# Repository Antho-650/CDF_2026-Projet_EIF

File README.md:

# CDF 2026 - Projet EIF

Dépôt officiel pour la participation à la Coupe de France de Robotique 2026.

## Documents et Suivi

Le suivi des achats (Excel/Google Sheets) et les documents administratifs sont sur le Google Drive du projet : https://drive.google.com/drive/u/1/folders/1xHnVBchuZF8TSyvHd5yfe0Ny8L7n_gqj

## Structure du dépôt

- **documents/** : Documents généraux du projet (spécifications, règlement, etc.)
- **robot_principal/** : Fichiers du robot principal
  - **electronique/** : Cartes électroniques (haut niveau, base mobile, actionneurs)
  - **mecanique/** : Conception mécanique (assemblage complet et sous-ensembles)
  - **code/** : Code embarqué (STM32) et code haut niveau (Raspberry Pi)
- **balises/** : Système de balises (électronique, code, mécanique)
- **pami_ninja/** : PAMI Ninja (électronique, mécanique, code)
- **pami_statique/** : PAMI Statique pour fin de match (électronique, mécanique, code)

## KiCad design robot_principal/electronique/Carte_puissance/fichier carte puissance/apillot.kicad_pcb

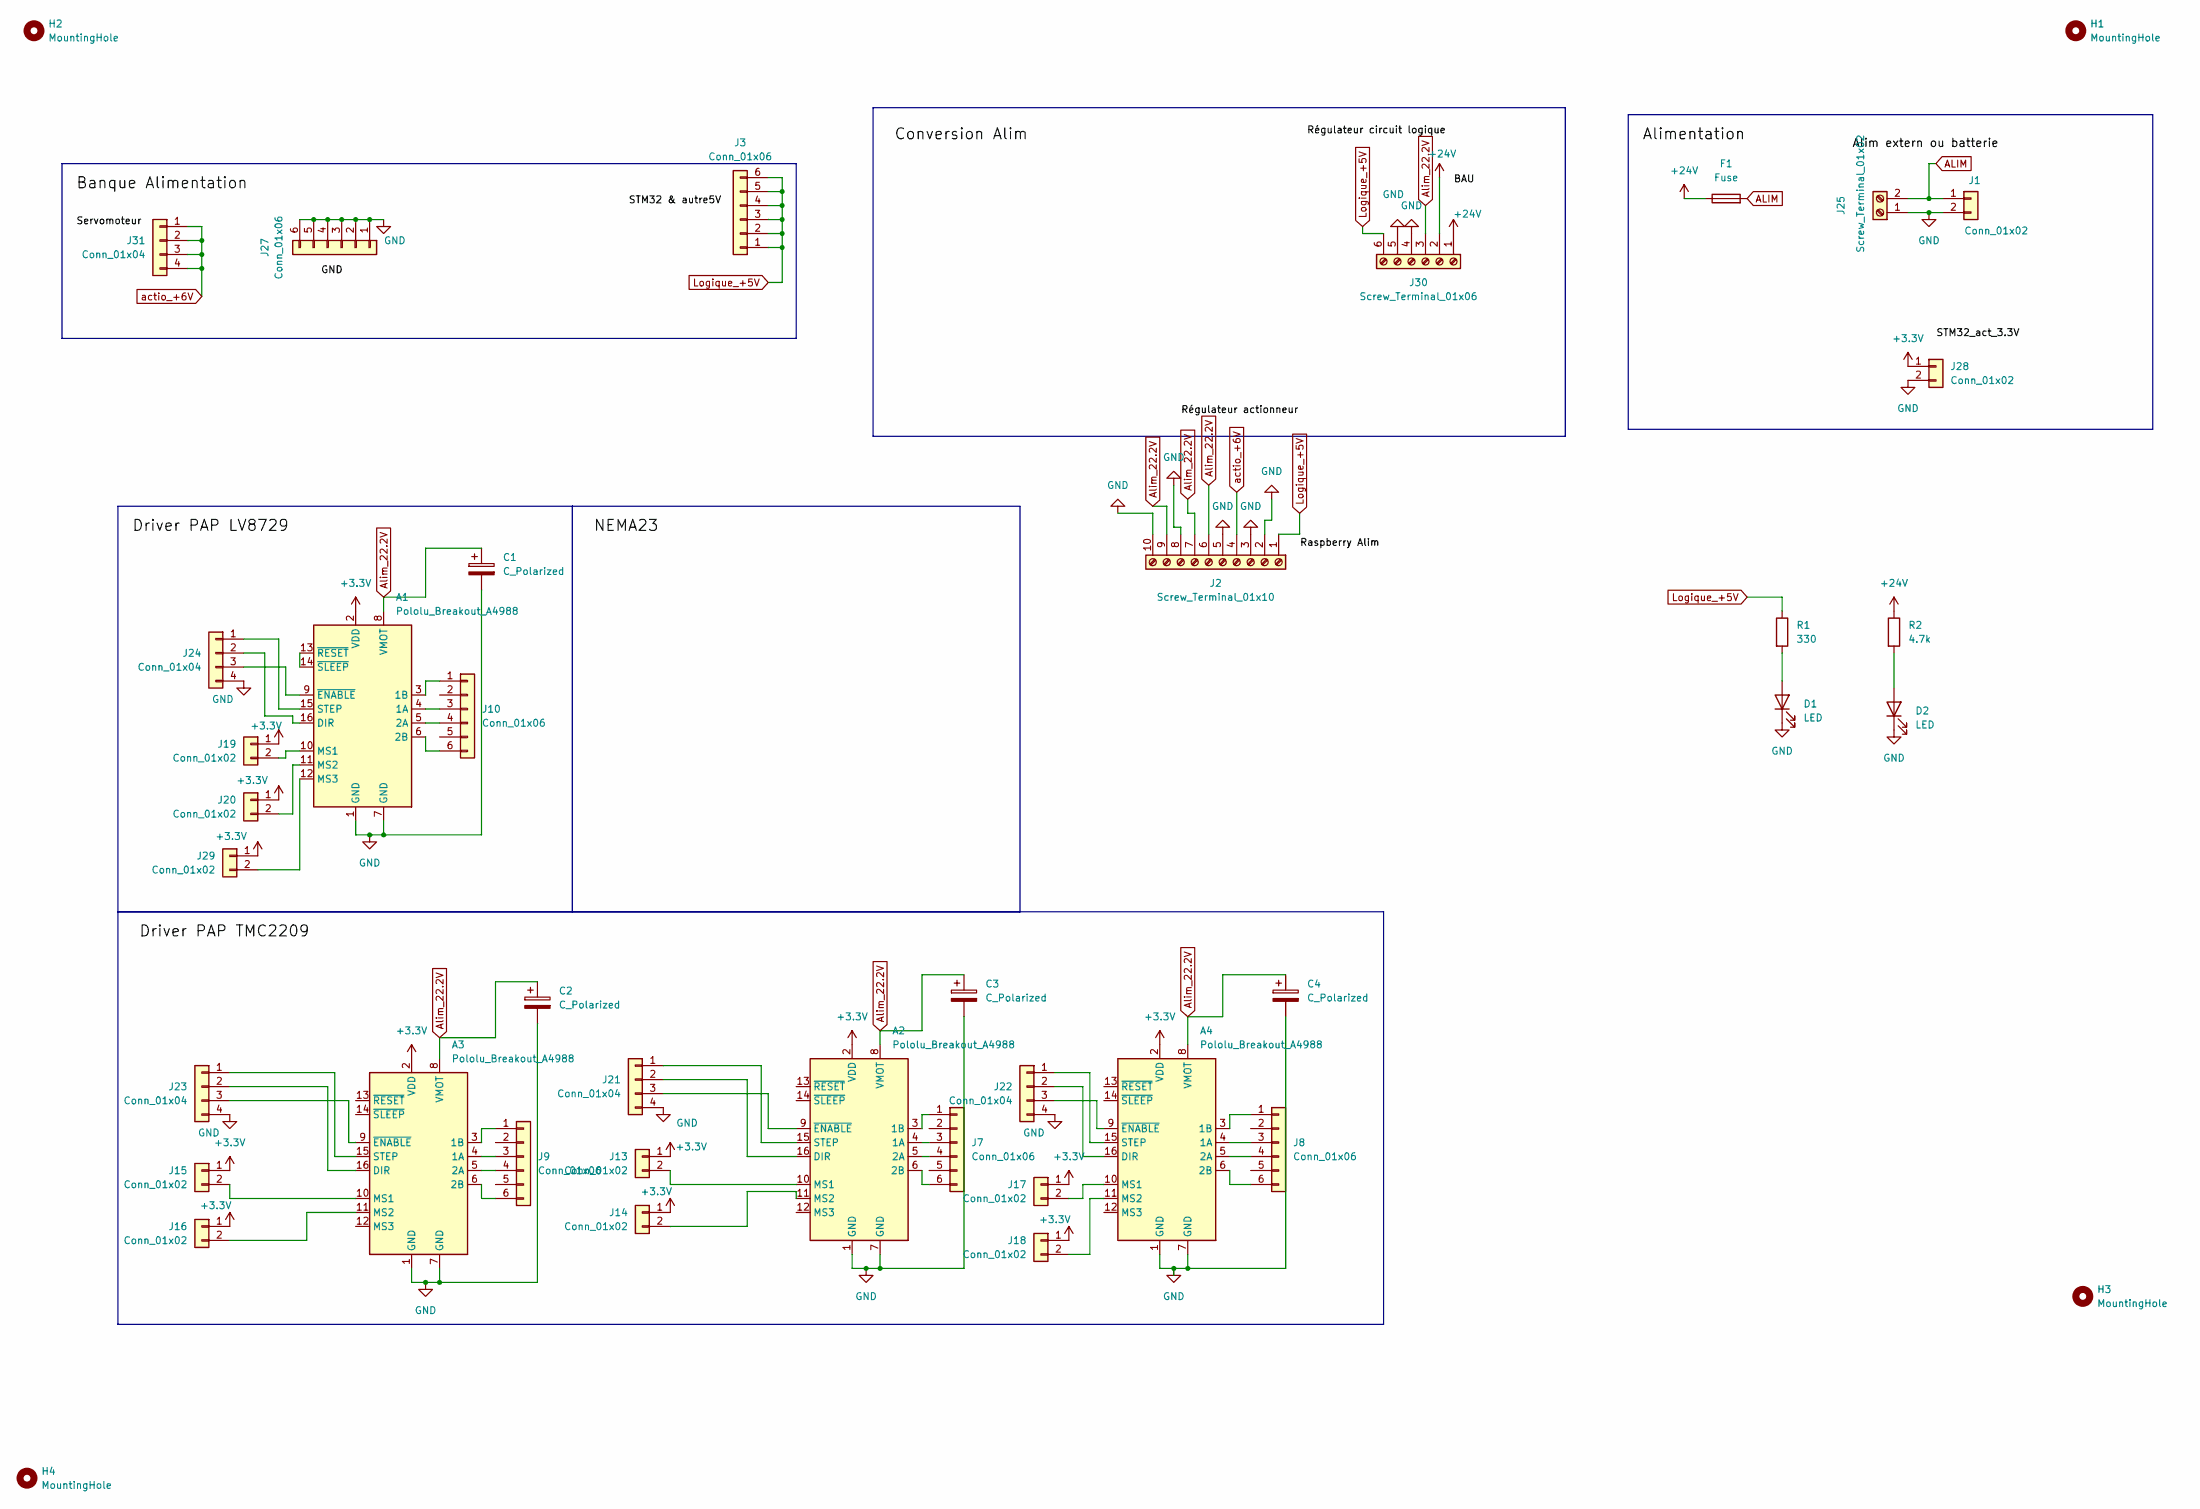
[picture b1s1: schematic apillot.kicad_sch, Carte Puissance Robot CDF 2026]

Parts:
A1, A2, A3, A4: Pololu_Breakout_A4988; Pololu_Breakout-16_15.2x20.3mm
C1, C2, C3, C4: C_Polarized; CP_Radial_D10.0mm_P5.00mm
D1, D2: LED; LED_D5.0mm
F1: Fuse; FuseHolder_Blade_ATO_Littelfuse_FLR_178.6165
H1, H2, H3, H4: MountingHole; MountingHole_3.2mm_M3
J1: Conn_01x02; AMASS_XT60-M_1x02_P7.20mm_Vertical
J2: Screw_Terminal_01x10; TerminalBlock_Phoenix_MKDS-1,5-10-5.08_1x10_P5.08mm_Horizon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
J3, J27: Conn_01x06; PinHeader_1x06_P2.54mm_Vertical
J7, J8, J9, J10: Conn_01x06; JST_XH_B6B-XH-A_1x06_P2.50mm_Vertical
J13, J14, J15, J16, J17, J18, J19, J20, J28, J29: Conn_01x02; PinHeader_1x02_P2.54mm_Vertical
J21, J22, J23, J24, J31: Conn_01x04; PinHeader_1x04_P2.54mm_Vertical
J25: Screw_Terminal_01x02; TerminalBlock_Phoenix_MKDS-1,5-2-5.08_1x02_P5.08mm_Horizont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
J30: Screw_Terminal_01x06; TerminalBlock_Phoenix_MKDS-1,5-6-5.08_1x06_P5.08mm_Horizont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
R1: 330; R_Axial_DIN0207_L6.3mm_D2.5mm_P10.16mm_Horizontal
R2: 4.7k; R_Axial_DIN0207_L6.3mm_D2.5mm_P10.16mm_Horizontal

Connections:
+3.3V: A1.2 (VDD), A2.2 (VDD), A3.2 (VDD), A4.2 (VDD), J13.1, J14.1, J15.1, J16.1, J17.1, J18.1, J19.1, J20.1, J28.1, J29.1
+24V: F1.1, J30.1, J30.2, R2.1
ALIM: F1.2, J1.1, J25.2
Alim_22.2V: A1.8 (VMOT), A2.8 (VMOT), A3.8 (VMOT), A4.8 (VMOT), C1.1, C2.1, C3.1, C4.1, J2.6, J2.7, J2.9, J30.3
GND: A1.1 (GND), A1.7 (GND), A2.1 (GND), A2.7 (GND), A3.1 (GND), A3.7 (GND), A4.1 (GND), A4.7 (GND), C1.2, C2.2, C3.2, C4.2, D1.1 (K), D2.1 (K), J1.2, J2.2, J2.3, J2.5, J2.8, J2.10, J21.4, J22.4, J23.4, J24.4, J25.1, J27.1, J27.2, J27.3, J27.4, J27.5, J27.6, J28.2, J30.4, J30.5
Logique_+5V: J2.1, J3.1, J3.2, J3.3, J3.4, J3.5, J3.6, J30.6, R1.1
unnamed: A1.4 (1A), J10.3
unnamed: A1.3 (1B), J10.1
unnamed: A1.5 (2A), J10.4
unnamed: A1.6 (2B), J10.6
unnamed: A1.16 (DIR), J24.2
unnamed: A1.10 (MS1), J19.2
unnamed: A1.11 (MS2), J20.2
unnamed: A1.12 (MS3), J29.2
unnamed: A1.15 (STEP), J24.1
unnamed: A1.9 (~ENABLE), J24.3
unnamed: A1.13 (~RESET), A1.14 (~SLEEP)
unnamed: A2.4 (1A), J7.3
unnamed: A2.3 (1B), J7.1
unnamed: A2.5 (2A), J7.4
unnamed: A2.6 (2B), J7.6
unnamed: A2.16 (DIR), J21.2
unnamed: A2.10 (MS1), J13.2
unnamed: A2.11 (MS2), J14.2
unnamed: A2.15 (STEP), J21.1
unnamed: A2.9 (~ENABLE), J21.3
unnamed: A3.4 (1A), J9.3
unnamed: A3.3 (1B), J9.1
unnamed: A3.5 (2A), J9.4
unnamed: A3.6 (2B), J9.6
unnamed: A3.16 (DIR), J23.2
unnamed: A3.10 (MS1), J15.2
unnamed: A3.11 (MS2), J16.2
unnamed: A3.15 (STEP), J23.1
unnamed: A3.9 (~ENABLE), J23.3
unnamed: A4.4 (1A), J8.3
unnamed: A4.3 (1B), J8.1
unnamed: A4.5 (2A), J8.4
unnamed: A4.6 (2B), J8.6
unnamed: A4.16 (DIR), J22.2
unnamed: A4.10 (MS1), J17.2
unnamed: A4.11 (MS2), J18.2
unnamed: A4.15 (STEP), J22.1
unnamed: A4.9 (~ENABLE), J22.3
unnamed: D1.2 (A), R1.2
unnamed: D2.2 (A), R2.2
actio_+6V: J2.4, J31.1, J31.2, J31.3, J31.4

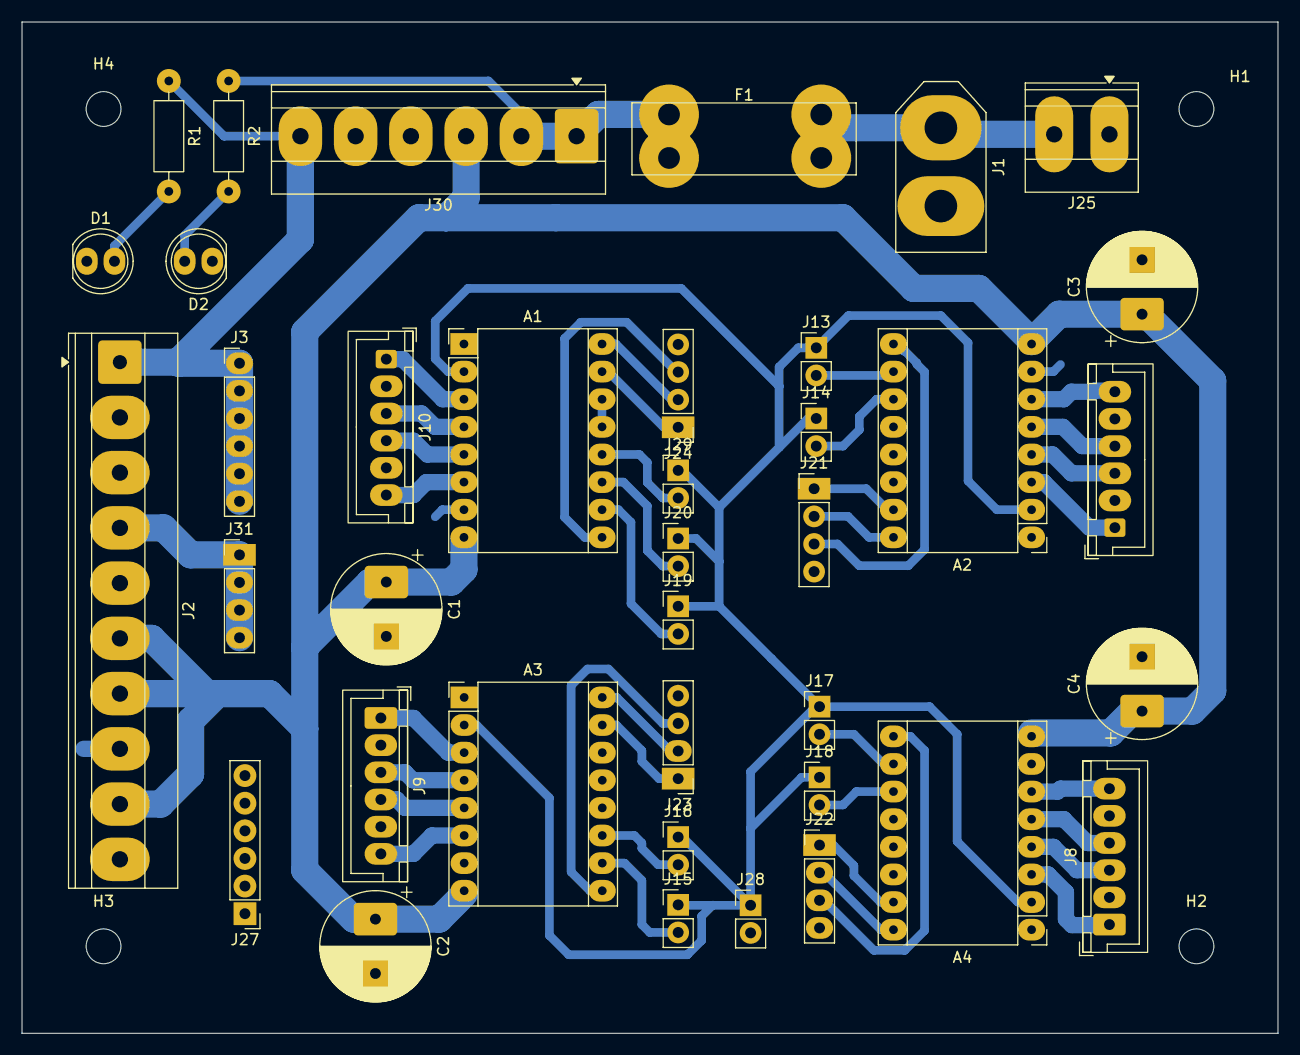
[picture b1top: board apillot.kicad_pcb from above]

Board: 2 copper layers, 115.5 x 93.0 mm, 42 parts (0 on the bottom side), 47 nets.

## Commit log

2025-12-19 Initial plan
2025-12-19 Create initial project structure with directories and README files
2025-12-19 Ajout des fichiers de documentations
2025-12-22 Ajout d'un dossier pour les datasheets des composants
2025-12-30 ajout de la datasheet du controleur escon 50/5
2025-12-30 ajout fichier pour le moteur maxon
    le fichier contenant les parametres du logiciel escon studio 2.2 (windows only) pour le controler d'un moteur maxon avec un réducteur de 100. et aussi de la capture d'écran des résultat du test de co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
2025-12-31 Ajout des datasheets pour les STM32
2026-01-01 Ajout du code de test pour le moteur maxon avec la carte stm32 (Nucleo L476RG)
2026-01-02 modification du fichier lien site matos : ajout d'un lien
2026-01-07 Ajout d'un fichier pour le lancement de la raspberry avec le LIDAR
2026-01-08 modif du fichier de lien et ajout fichier pour le lidar et raspberry
2026-01-08 ajout d'un fichier pour utiliser git
2026-01-20 ajout fichier fonctionnement git, ajout de test lidar avec respberry
2026-01-29 modifications fichier lien site matos
2026-01-29 Add PlatformIO directories to .gitignore
2026-01-29 Création programme test pour moteur pas à pas dans robot carte actionneur
2026-02-04 ajout devis pour achat
2026-02-04 config pas mal
2026-02-11 Fix STEPS_TARGET calculation and add infinite loop to halt program after one rotation
2026-02-26 change nom dossier pour enlever espace pour windows
2026-02-26 ajout datasheet nucleo et debut PCB carte puissance
2026-03-10 carte elec de puissance terminée
2026-03-11 Carte elec fini, demande gravure faite
